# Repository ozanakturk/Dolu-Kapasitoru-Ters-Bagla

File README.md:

# EE463 Project Github Repo of Dolu Kapasitörü Ters Tut

Ozan Aktürk 2303923

İsa Ersöz 237498

Selin Ezgi Özcan 2375475

Original Project Repo: https://github.com/odtu/ee463/tree/master/Term%20Project

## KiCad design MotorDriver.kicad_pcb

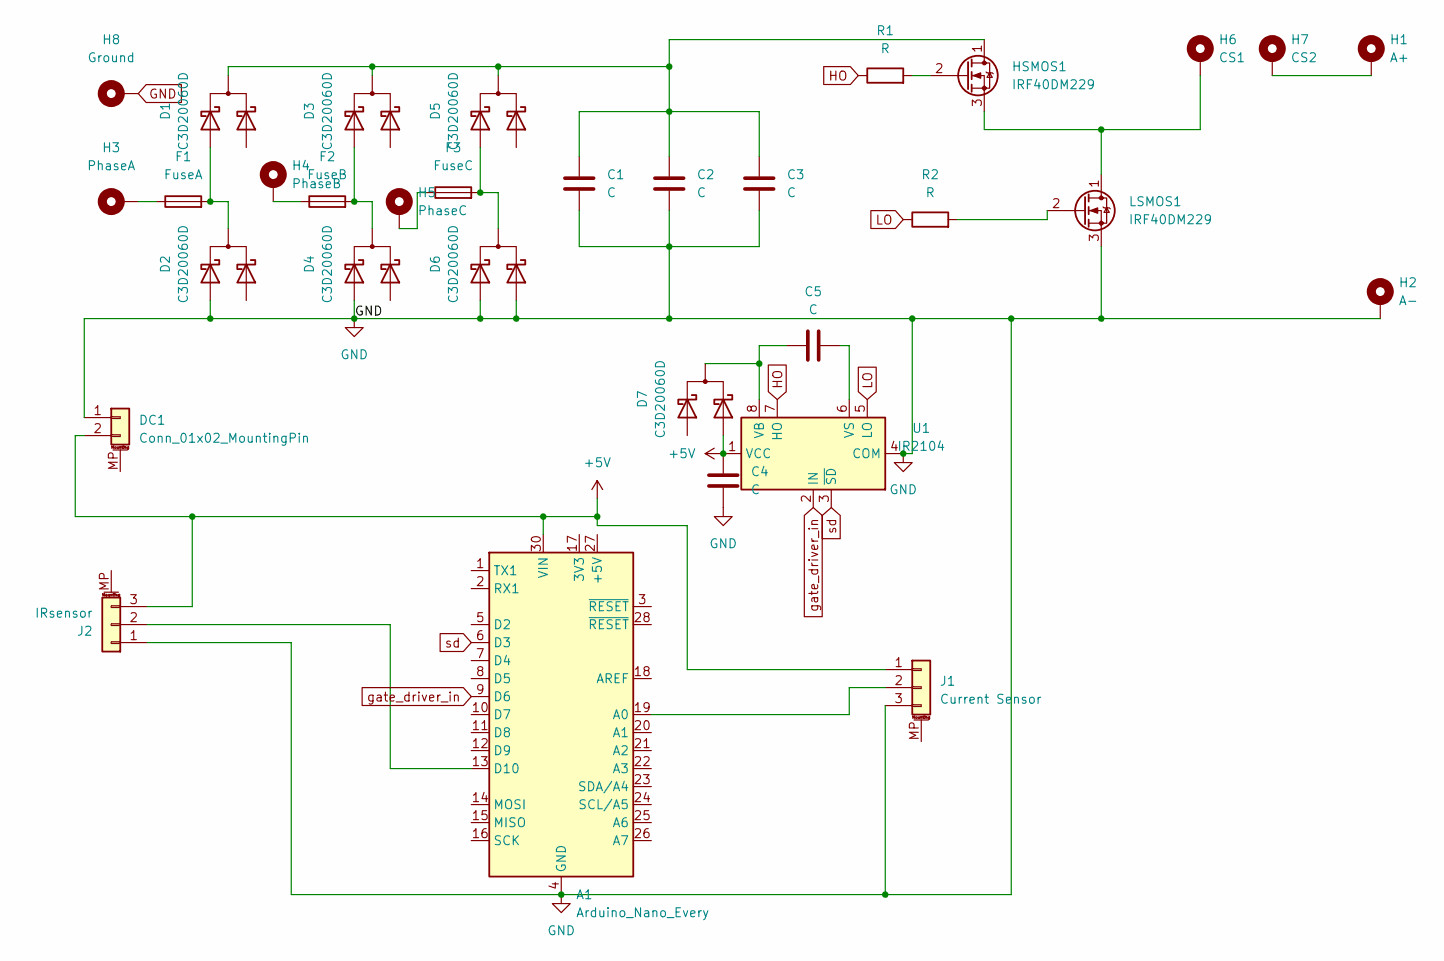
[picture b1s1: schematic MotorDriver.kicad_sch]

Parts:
A1: Arduino_Nano_Every; Arduino_Nano
C1, C2, C3: C; CP_Axial_L30.0mm_D12.5mm_P35.00mm_Horizontal
C4, C5: C; CP_Axial_L10.0mm_D6.0mm_P15.00mm_Horizontal
D1, D2, D3, D4, D5, D6, D7: C3D20060D; TO-247-3_Vertical
DC1: Conn_01x02_MountingPin; Banana_Jack_2Pin
F1: FuseA; Fuseholder_Cylinder-5x20mm_Schurter_0031_8201_Horizontal_Op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
F2: FuseB; Fuseholder_Cylinder-5x20mm_Schurter_0031_8201_Horizontal_Op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
F3: FuseC; Fuseholder_Cylinder-5x20mm_Schurter_0031_8201_Horizontal_Op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
H1: A+; Banana_Jack_1Pin
H2: A-; Banana_Jack_1Pin
H3: PhaseA; Banana_Jack_1Pin
H4: PhaseB; Banana_Jack_1Pin
H5: PhaseC; Banana_Jack_1Pin
H6: CS1; Banana_Jack_1Pin
H7: CS2; Banana_Jack_1Pin
H8: Ground; Banana_Jack_1Pin
HSMOS1: IRF40DM229; TO-220-3_Vertical
J1: Current Sensor; PinHeader_1x03_P2.54mm_Vertical
J2: IRsensor; PinHeader_1x03_P2.54mm_Vertical
LSMOS1: IRF40DM229; TO-220-3_Vertical
R1, R2: R; R_Axial_DIN0414_L11.9mm_D4.5mm_P5.08mm_Vertical
U1: IR2104; DIP-8_W10.16mm_LongPads

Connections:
+5V: A1.30 (VIN), C4.1, D7.3 (A2), DC1.2, J1.1, J2.3, U1.1 (VCC)
GND: A1.4 (GND), A1.29 (GND), C1.2, C2.2, C3.2, C4.2, D2.1 (A1), D4.1 (A1), D6.1 (A1), D6.3 (A2), DC1.1, H2.1, H8.1, J1.3, J2.1, LSMOS1.3 (S), U1.4 (COM)
HO: R1.1, U1.7 (HO)
LO: R2.1, U1.5 (LO)
unnamed: A1.13 (D10), J2.2
unnamed: A1.19 (A0), J1.2
unnamed: C1.1, C2.1, C3.1, D1.2 (K), D3.2 (K), D5.2 (K), HSMOS1.1 (D)
unnamed: C5.2, U1.6 (VS)
unnamed: D1.1 (A1), D2.2 (K), F1.2
unnamed: D3.1 (A1), D4.2 (K), F2.2
unnamed: D5.1 (A1), D6.2 (K), F3.2
unnamed: C5.1, D7.2 (K), U1.8 (VB)
unnamed: F1.1, H3.1
unnamed: F2.1, H4.1
unnamed: H1.1, H7.1
unnamed: F3.1, H5.1
unnamed: HSMOS1.2 (G), R1.2
unnamed: H6.1, HSMOS1.3 (S), LSMOS1.1 (D)
unnamed: LSMOS1.2 (G), R2.2
gate_driver_in: A1.9 (D6), U1.2 (IN)
sd: A1.6 (D3), U1.3 (~SD)

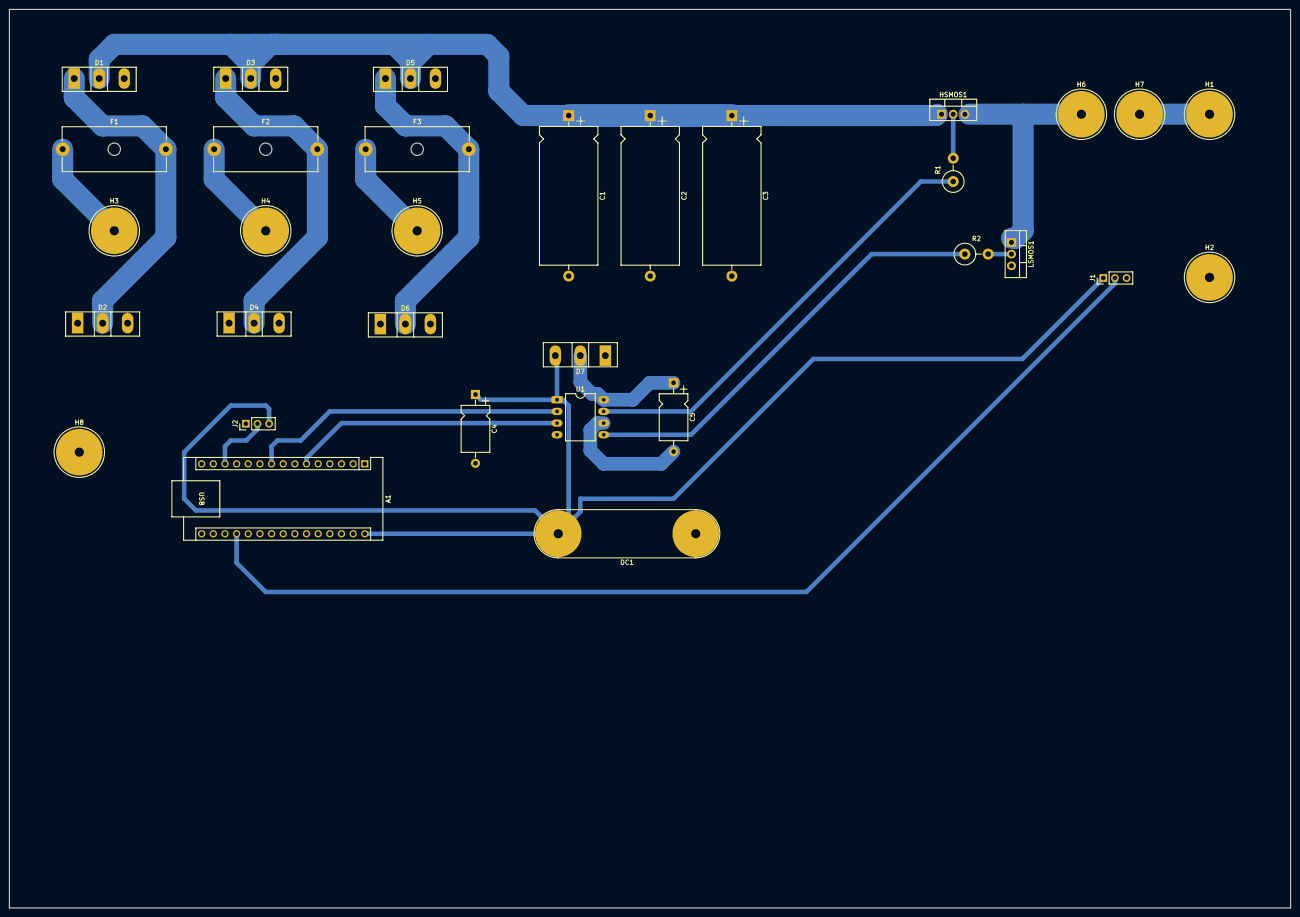
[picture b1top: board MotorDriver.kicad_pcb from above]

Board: 2 copper layers, 279.3 x 195.9 mm, 32 parts (0 on the bottom side), 21 nets.

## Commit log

2022-11-20 Added two main topologies
2022-11-21 Edited simulations & added flyback circuit photo
2022-11-29 Improved versions of the main topologies
2022-12-06 Create flyback links
    i found some papers on flyback converters. may be worth to take a look
2022-12-06 added two switch forward converter
2022-12-08 simulation with sync buck and dc motor
2022-12-10 Lt spice model of our model
2022-12-10 Add Hall Sensor video link
2022-12-10 Control loop
2022-12-10 Control loop edited
2022-12-10 Added the simulation report
2022-12-12 Add current and speed sensor video links
2022-12-12 Added ACS724 links
2022-12-13 Add component list (13.12.2022)
2022-12-13 Add order screenshots
2022-12-27 Bootstrap link added
2023-01-01 Board Design - Needs reviewing and editing
    Any comment and criticism are not only welcome but also needed. :)
2023-01-04 Current sensor tests on arduino
2023-01-05 Add arduino codes
2023-01-09 added the whole kicad project
2023-01-10 Spice & arduino code changes
2023-01-10 Adjustments on arduino codes
2023-01-10 Added farewell code
2023-01-24 Add Final Report components
